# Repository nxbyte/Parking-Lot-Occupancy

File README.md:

# Parking Lot Occupancy

Undergraduate Senior Project focusing on detecting vehicle occupancy for parking lots

## Abstract

As The College of New Jersey increases its student and faculty size, there is an ever increasing need to manage its growth appropriately. One area in particular need of attention is parking on campus. Currently, many commuting facility, staff, and students attempt to find available parking spaces by driving around to different parking lots and guessing where parking spaces may be available.

The **Parking Lot Availability and Traffic Prediction System** provides commuters with information about the availability of free parking spaces, which will not only alleviate traffic congestion but also increase coordination for commuters. This system is made up of three components: detection nodes to detect vehicles entering and exiting parking lots, a base station that will host a wireless network to collect traffic data from each detection node, and a web server to provide current parking space availability at a glance. Each detection unit contains: sensors, wireless radio, and custom solar charging circuit for renewable outdoor operation. The base station contains a microcomputer and a wireless radio to communicate with each detection unit. All traffic data is securely stored and displayed on an Amazon web server which is accessible to TCNJ commuters. The final product allows commuters to view the status of open spaces and make The College of New Jersey a better and more coordinated campus. This system can be adapted to any environment with a gate and/or a road.

## Overall Architecture

## Credits

**Core Team**

- Warren Seto (Computer Engineer, Class of 2018)
- Nikita Eisenhauer (Electrical Engineer, Class of 2018)
- Stephanie Fournier (Electrical Engineer, Class of 2018)
- Matthew Cook (Computer Engineer, Class of 2018)
- Dr. Larry Pearlstein (Advisor)

**With help from...**

- Michael Steeil (TCNJ Engineering Laboratory Technician)
- Grant Cignarella (Mechanical Engineer, Class of 2020)
- Joshua Acker (Mechanical Engineer, Class of 2018)
- Lindsey Abramson (Computer Science, Class of 2018)
- Elisa Idrobo (Computer Science, Class of 2018)
- Philip Franco (Electrical Engineer, Class of 2019)
- Justin Cheng (Mechanical Engineer, Class of 2017)

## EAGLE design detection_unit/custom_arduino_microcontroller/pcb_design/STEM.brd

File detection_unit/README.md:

# Detection Unit

The Detection Unit is a device that is placed at the entrance and exit to each of the parking lots that are to be monitored with the system. 

**Each Detection Unit includes the following:**

- Microcontroller and sensor package, called Detection Unit Core
- Power subsystem, which includes solar panels, battery and associated electronics
- A 3D printed enclosure

## Microcontrollers

##### Adafruit Feather 32u4
The Adafruit Feather 32u4 microcontroller is an Arduino based microcontroller. The sensor has an onboard LoRa radio. The microcontroller uses SPI to communicate with the LoRa radio. The 32u4 also features an I2C interface, many different pins for GPIO, Digital IO, Analog IO, an antenna pin, a power cable connector for connecting to a power source, and a micro-USB port for power and programming.

##### Custom Arduino Microcontroller
The idea to make a PCB of an Arduino Uno was proposed to save cost, have experience with PCB CAD, and conserve space in the enclosure. The program used to design the PCB is Eagle CAD due to its compatibility with printing companies and its popularity allowing the user to have access to many tutorials. In order to build the Arduino, it is necessary to know the components used in an Arduino that will be needed in the PCB and all the hardware that will be needing the Arduino.

## Sensors & Peripherals

##### Ultrasonic Sensor
The Maxbotix LV-MaxSonar-EZ1 Ultrasonic Range Finder is an ultrasonic sensor that uses Analog output to communicate with a host microcontroller. Ultrasonic sensors emit ultrasonic pulses that can bounce off objects and calculate the distance based on the amount of time sound takes to reach the sensor. The sensor has a theoretical detection range of 6.45 meters from is initial position. Each Detection Unit Core uses one of these sensors positioned towards the curb of a street. The Ultrasonic Range Finder is used to detect whether a vehicle is passing by the Detection Unit.

##### Time of Flight Infrared Sensor
The Adafruit VL53L0X Time of Flight Distance Sensor is a LIDAR sensor that uses I2C to communicate with a host microcontroller. LIDAR is a technology that uses laser light pulses to determine the distance between the sensor and the object in front of the sensor. The sensor has a theoretical detection range of up to one meter from is initial position. Each Detection Unit Core uses one of these sensors positioned upwards the gate above the Detection Unit. The Time of Flight Sensor is used to detect the position of the gate and verify that an authorized vehicle has passed through the entrance of a parking lot. 

## Detection Algorithm

To accurately detect a vehicle, the group wanted to use all current infrastructure already setup in the parking lot such as the limited roadways and established gate units at the entrance. After researching into possible sensors to sense the state of the entrance, the group chose two types of sensors to go into each Detection Unit. The first sensor, the Maxbotix LV-MaxSonar-EZ1 Ultrasonic Range Finder, is tasked with detecting whether an entity (vehicle or animal) enters the parking lot. The Ultrasonic Range Finder, has a theoretical detection range of 6.45 meters (645 cm). After testing the sensor in the field, the sensor actually had a detection range of 4.5 meters (450 cm) which still satisfied the group’s detection requirements of detecting an entity on a 325 cm roadway. The first sensor, the Adafruit VL53L0X Time of Flight Distance Sensor, is tasked with detecting whether a given object entering the lot is authorized to enter by determining the position of the gate unit. The group determined that an authorized vehicle would make the gate rise which would be detected by the Distance sensor. The Time of Flight Distance Sensor, has a theoretical detection range of two meters (200 cm). After testing the sensor in the field, the sensor was tuned and scaled to sense a meter which satisfied the group’s detection requirements of detecting the gate at rest which was 92 cm above the island. Before any hardware was used for detection, the group calibrated each sensor with the gate and roadway in the entrance of the parking lot.

Through testing with driving vehicles through the entrance of the parking lot multiple times, the group determined that the Detection Unit will count an object as a valid vehicle entering the parking lot when both sensors reach a certain state. When the entrance to a parking lot has no vehicles entering, the ultrasonic sensor would read the maximum range value (approximately 450 cm) and the infrared distance sensor would read a constant 92 cm. When a vehicle enters the parking lot, the ultrasonic sensor would detect a drop in distance over a period of 4 seconds which will cause the infrared distance sensor to begin tracking the position of the gate unit for 5 seconds. Since the gate unit is near the maximum range of the distance sensor, when the gate unit opens the distance sensor will output the maximum range (2 meters). When both the ultrasonic sensor reads a drop in distance and the infrared distance sensor outputs its maximum range value, a vehicle is counted and sent to a centralized server. After performing various experiments with 100 entering vehicles, the group found that this method allowed the Detection Unit to detect 98% of authorized vehicles entering the parking lot. 

## Power Subsystem

Large pre-existing parking lots offer limited external power connections AC power, and the addition of such connections would be costly. Laying wires would present safety concerns for drivers and cumbersome gantry supports to allow overhead connections would be impractical. To minimize the burden of deployment of detection units in a large number of parking lots at TCNJ, we provide autonomous power to each detection unit, without requiring a connection to an AC power line. Stable, continuous power is required for proper operation of the detection unit subsystems and components.  A compact and standalone solar system was developed for use with each unit, allowing for greater freedom of placement and minimal external wiring as compared to alternative energy sources such as wind. Solar also provided scalable power as opposed to a much more restricted low power energy harvesting system. Charge storage in the event of poor solar insolation due to bad weather and for overnight detection unit power demands was accounted for with a LiPo battery charging circuit. LiPo batteries being available in significantly smaller packages than their Lithium-Ion battery counterparts allowed for the design of a smaller waterproof enclosure. To ensure battery longevity and safety, circuit elements to provide overcurrent and voltage regulation protection were included. Additionally, a DC/DC boost converter was necessary to account for the unique power demands and losses of the individual detection unit components. 

## Enclosure

A major component of this project is the detection system that relays the information of the sensors to the base station and the power system that powers the detection system using a solar panel. In order to keep all the components of each system in place and intact, an enclosure for the detection unit was proposed. Along with verifying that the hardware of these systems would be secure from the environment, it acts as a mount for the sensors to detect the moving vehicles. The design of the enclosure was based on the needs previously mentioned above and due to trial error, there are five versions of the first prototype all designed using CAD in Autodesk Fusion 360.

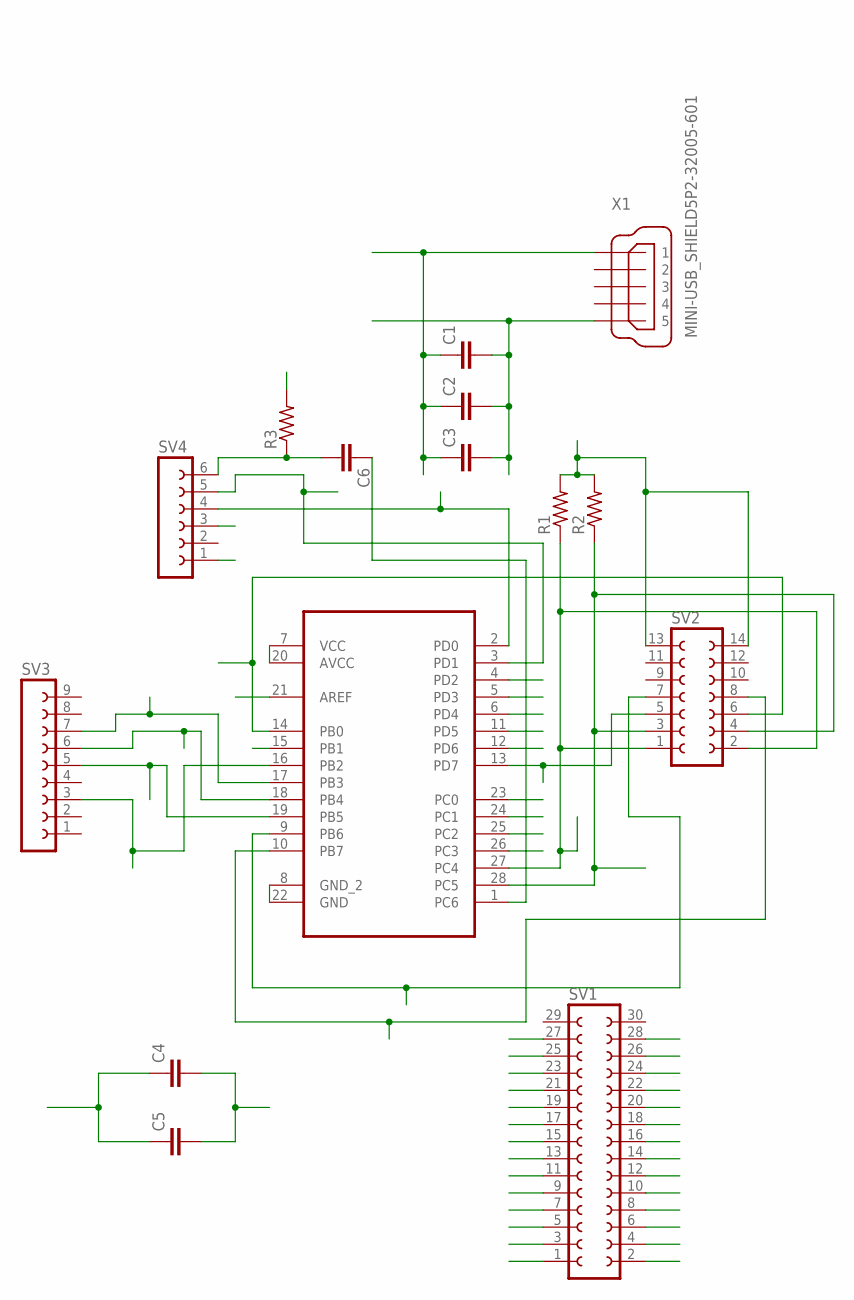
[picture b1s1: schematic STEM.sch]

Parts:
C1, C2, C3, C4, C5, C6: C2,5-3; C2.5-3
R1, R2, R3: R-US_0204/7; 0204/7
SV1: FE15-2
SV2: FE07-2
SV3: FE09-1; FE09
SV4: FE06-1; FE06
U1: ATMEGA328P-PU; DIP254P762X457-28
X1: MINI-USB_SHIELD5P2-32005-601; 32005-601

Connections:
AREF: C4.1, C5.1, SV1.14, U1.21 (AREF)
GND: C1.2, C2.2, C3.2, C4.2, C5.2, SV1.13, SV1.16, SV4.1, U1.8 (GND_2), U1.22 (GND), X1.5
PB0: SV1.1, SV2.6, U1.14 (PB0)
PB1: SV1.2, U1.15 (PB1)
PB2: SV1.4, SV3.3, U1.16 (PB2)
PB3: SV1.6, SV3.7, U1.17 (PB3)
PB4: SV1.8, SV3.6, U1.18 (PB4)
PB5: SV1.10, SV3.5, U1.19 (PB5)
PB6: SV1.11, SV2.7, U1.9 (PB6)
PB7: SV1.9, SV2.8, U1.10 (PB7)
PC0: SV1.18, U1.23 (PC0)
PC1: SV1.20, U1.24 (PC1)
PC2: SV1.22, U1.25 (PC2)
PC3: SV1.24, U1.26 (PC3)
PC4: R1.1, SV1.26, SV2.1, SV2.2, U1.27 (PC4)
PC5: R2.1, SV1.28, SV2.3, SV2.4, U1.28 (PC5)
PC6: C6.1, SV1.27, U1.1 (PC6)
PC62: C6.2, R3.1, SV4.6
PD0: SV1.25, SV4.4, U1.2 (PD0)
PD1: SV1.23, SV4.5, U1.3 (PD1)
PD2: SV1.21, U1.4 (PD2)
PD3: SV1.19, U1.5 (PD3)
PD4: SV1.17, U1.6 (PD4)
PD5: SV1.7, U1.11 (PD5)
PD6: SV1.5, U1.12 (PD6)
PD7: SV1.3, SV2.5, U1.13 (PD7)
VCC: C1.1, C2.1, C3.1, R1.2, R2.2, R3.2, SV1.12, SV1.15, SV2.13, SV2.14, SV4.3, U1.7 (VCC), U1.20 (AVCC), X1.1

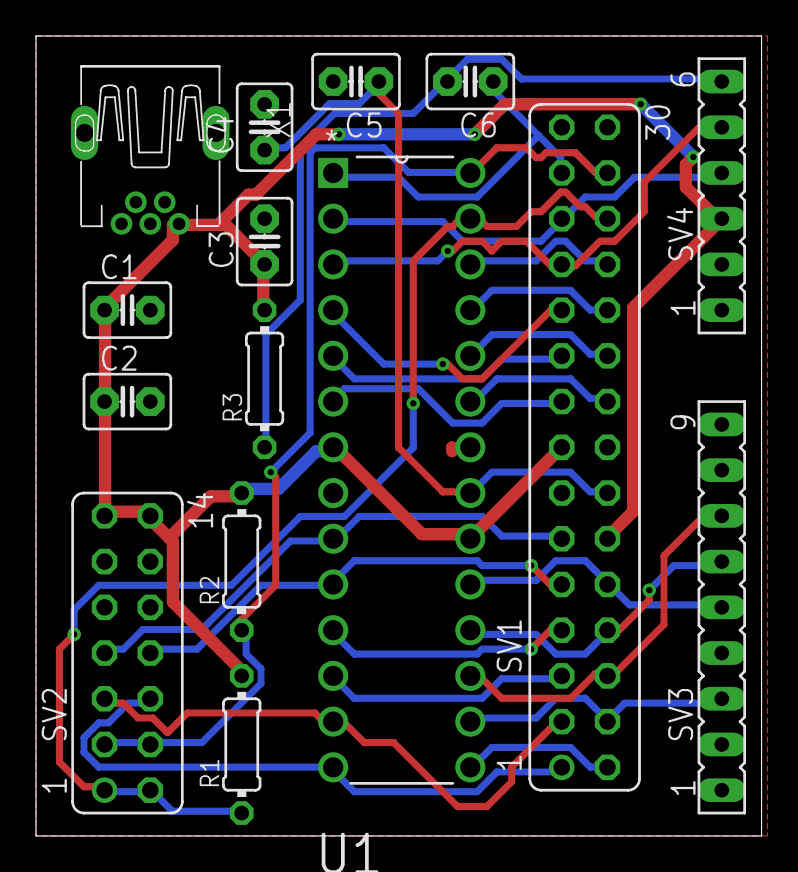
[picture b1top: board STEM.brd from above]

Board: 2 copper layers, 40.3 x 44.4 mm, 15 parts (0 on the bottom side), 27 nets.

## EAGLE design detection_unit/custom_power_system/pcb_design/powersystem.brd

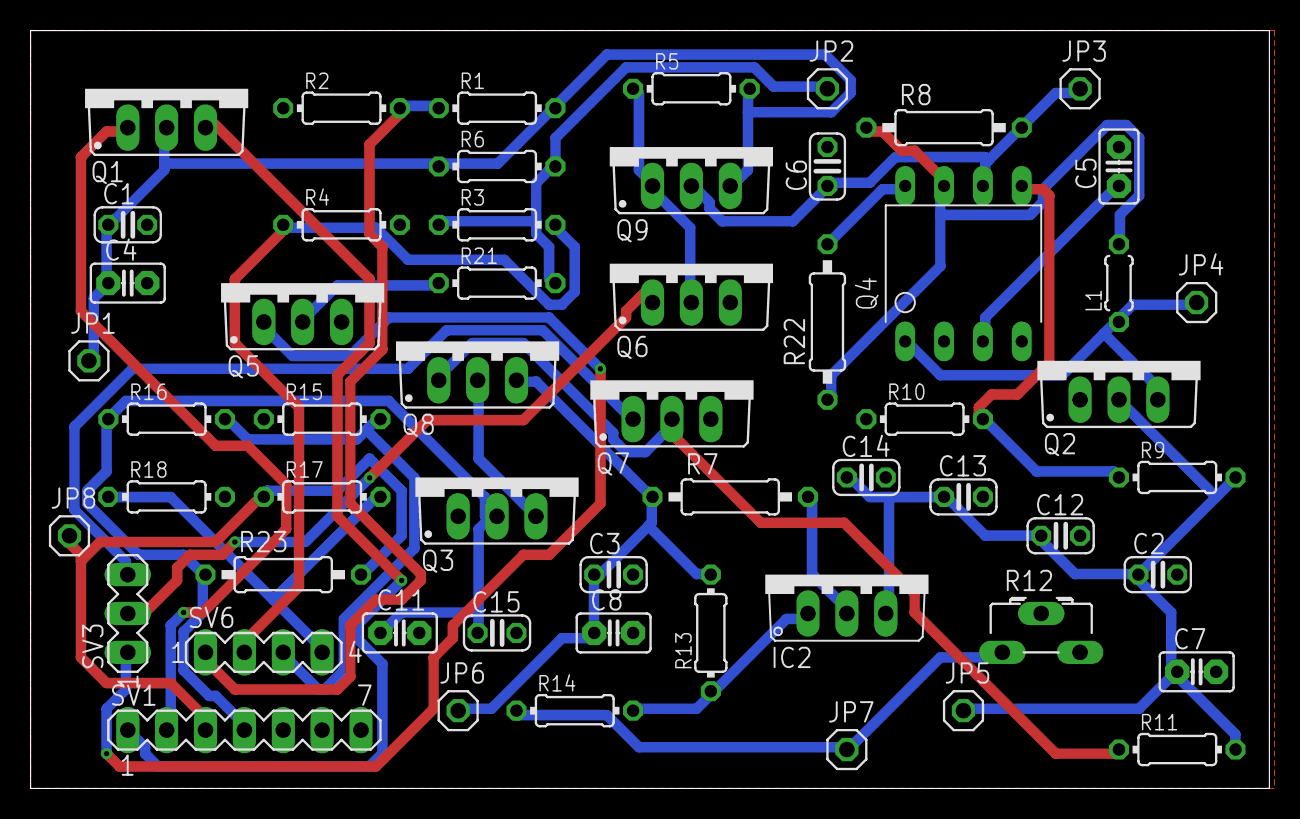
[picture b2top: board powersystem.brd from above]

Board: 2 copper layers, 81.0 x 49.5 mm, 56 parts (0 on the bottom side), 29 nets.

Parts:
C1, C2, C3, C6, C12, C13, C14, C15: C025-024X044
C4, C5, C7, C8, C11: C2.5-2
IC2: MC33269T; TO220V
JP1, JP2, JP3, JP4, JP5, JP6, JP7, JP8: 1X01
L1: 0204/5
Q1, Q2, Q3, Q5, Q6, Q7, Q8, Q9: TO220BV
Q4: UCC38050; DIP-8
R1, R2, R3, R4, R5, R6, R9, R10, R11, R13, R14, R15, R16, R17, R18, R21: 0204/7
R7, R8, R22, R23: 0207/10
R12: CA6H
SV1: MA07-1
SV3: MA03-1
SV6: MA04-1

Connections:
BATTERY: JP8.1, R17.1, R23.2, SV1.3
BATTERYLEFT: R15.2, R16.2, SV6.3
BATTERYRIGHT: R17.2, R18.1, SV6.4
BETWEENRESISTOR: JP2.1, R3.1, R6.2, R21.2
DIODE1: C1.1, C4.1, JP1.1, Q1.D, Q9.S, R1.2, R5.2, R6.1
DUMMYLOADBOTTOM: R3.2, R4.1, SV6.2
DUMMYLOADSWITCH: Q5.G, SV3.1
DUMMYLOADTOP: R1.1, R2.2, SV6.1
GND: C1.2, C2.2, C3.2, C4.2, C5.2, C6.2, C7.2, C8.2, C11.2, C12.2, C13.2, C14.2, C15.2, Q4.2, Q4.4, Q5.S, Q6.S, Q7.S, R2.1, R4.2, R10.1, R12.S, R15.1, R18.2, SV1.5, SV1.6, SV1.7
LOAD: C11.1, C15.1, Q3.D, R16.1, R23.1, SV1.4
unnamed: Q6.D, Q9.G, R5.1
unnamed: Q4.5, R9.1, R10.2
unnamed: Q4.8, R22.2
unnamed: Q7.D, Q8.G, R11.1
unnamed: IC2.1, R13.1, R14.2
unnamed: Q3.S, Q8.D
unnamed: Q5.D, R21.1
unnamed: IC2.2, R7.2
unnamed: L1.2, Q4.7, R8.1, R22.1
unnamed: C5.1, Q4.3
PINOUT1: JP4.1, L1.1, Q2.S, Q4.1
PINOUT6: C6.1, JP3.1, Q4.6, Q9.D, R8.2
POT: JP7.1, R12.A, R14.1
PRIMARYNOSUNLIGHT: Q6.G, SV3.2
SECONDARYNOSUNLIGHT: Q7.G, SV3.3
SOLARPANEL1: Q1.S, SV1.1
SOLARPANEL2: Q1.G, SV1.2
VINREG: C2.1, C7.1, C12.1, C13.1, C14.1, IC2.3, JP5.1, Q2.D, R9.2, R11.2
VOUTREG: C3.1, C8.1, JP6.1, Q8.S, R7.1, R13.2

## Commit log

2018-04-22 Initial Commit
    - Added source files for the following modules: Detection Unit, Base Station, and Web Server
2018-04-22 Added Base Station Utilities
2018-04-22 Added documentation for each module
2018-04-22 Re-structured repository
2018-04-22 Added comprehensive documentation
2018-04-22 Added graph to detection units documentation
2018-04-22 Added Power Subsystem schematic

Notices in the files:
README.md:
License: MIT
